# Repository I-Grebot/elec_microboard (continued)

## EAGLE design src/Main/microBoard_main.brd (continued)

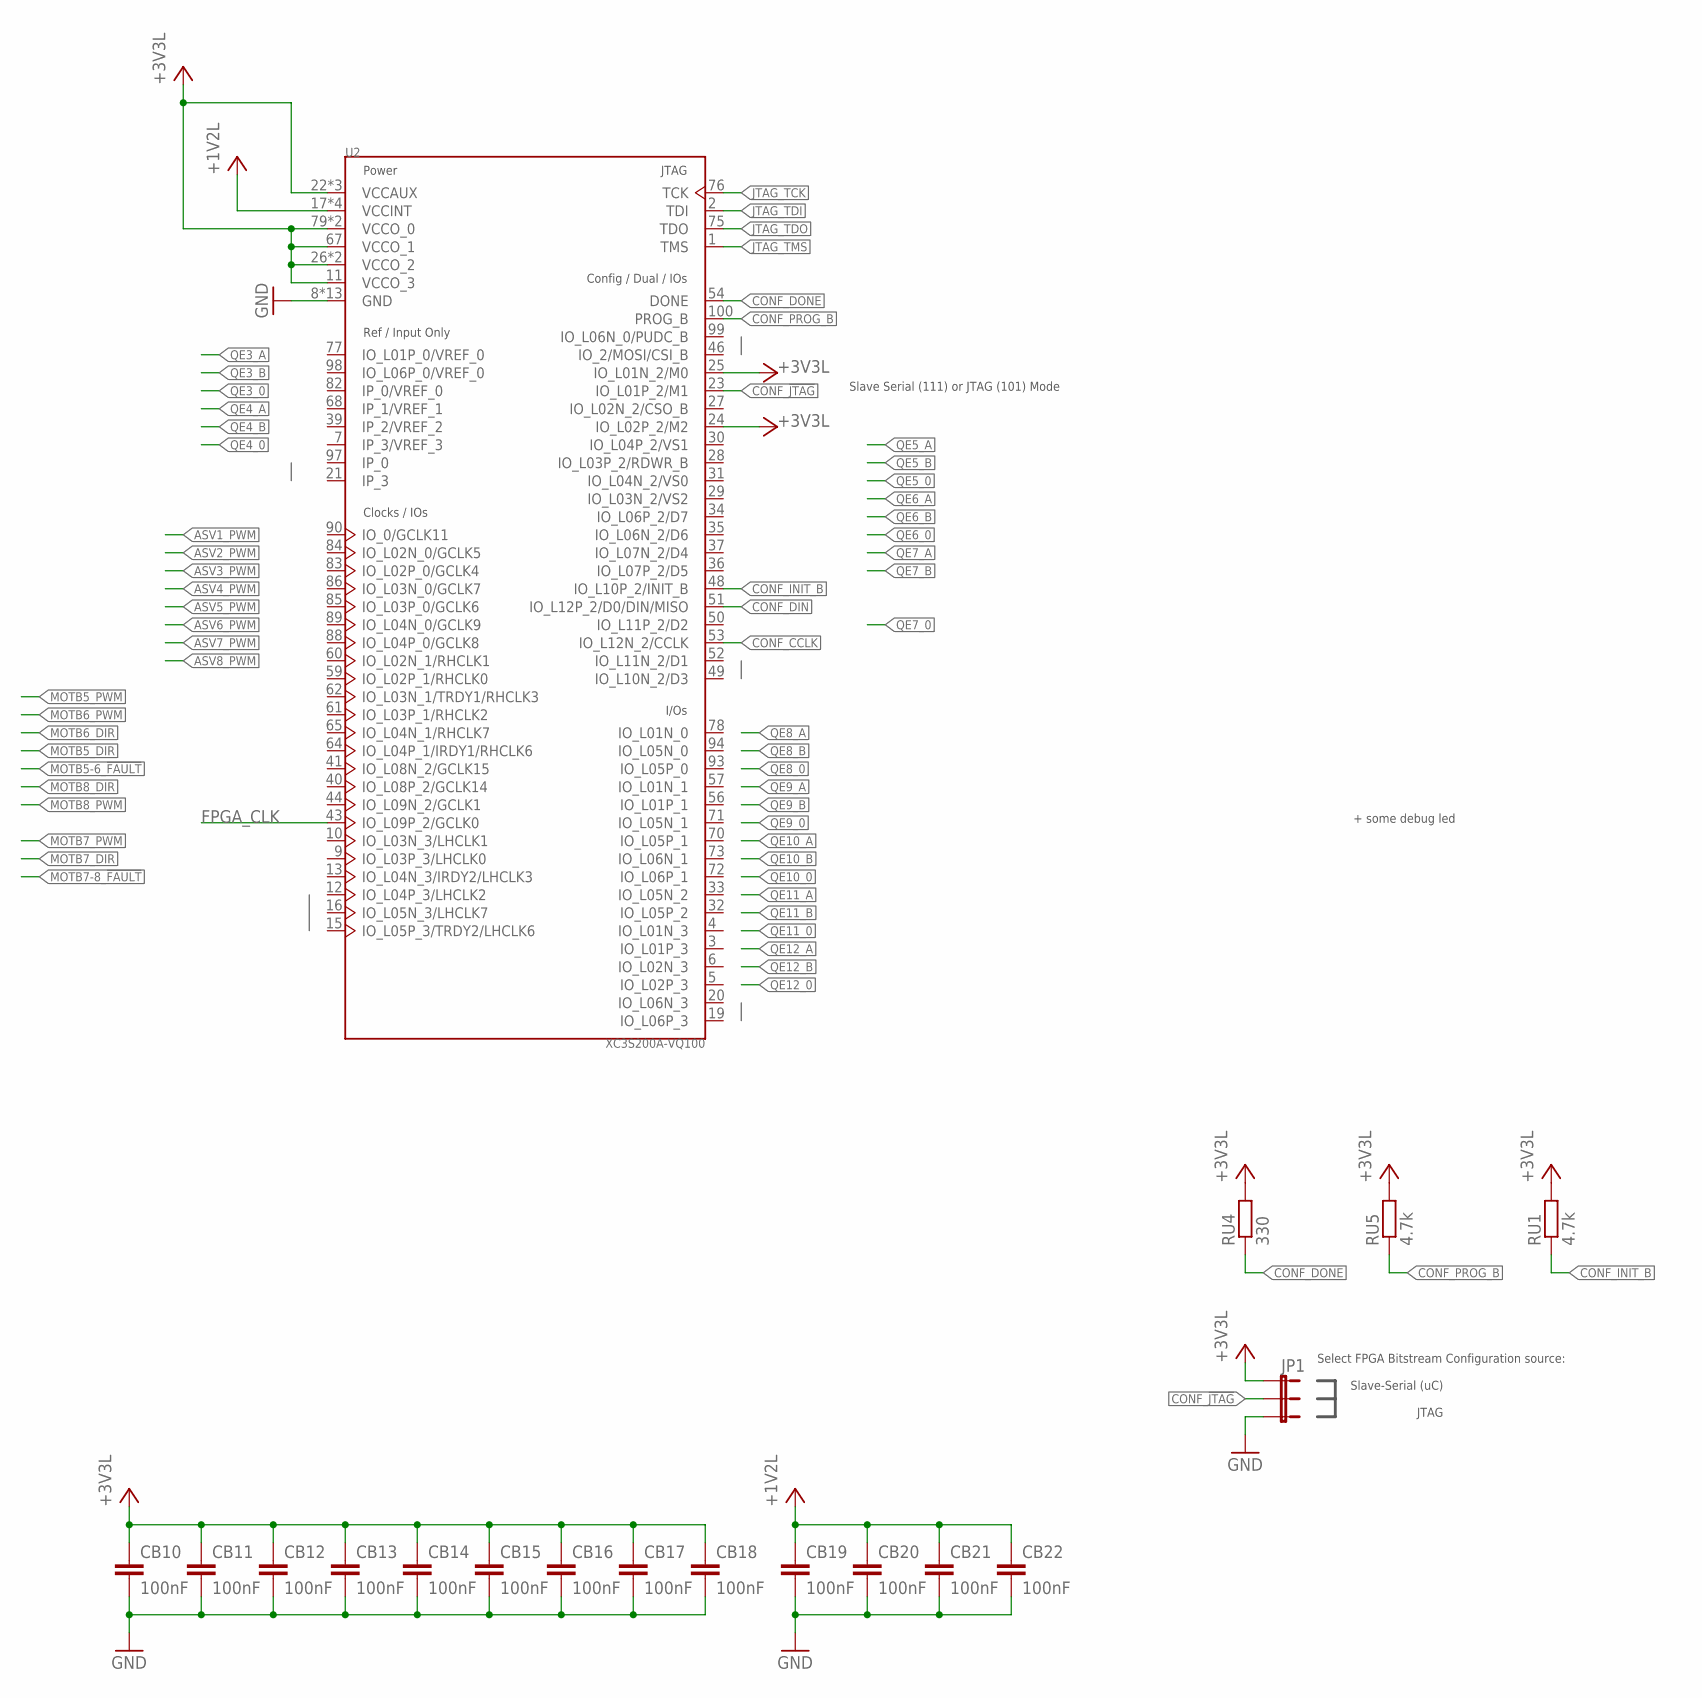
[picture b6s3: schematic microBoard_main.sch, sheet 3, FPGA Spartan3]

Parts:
CB10, CB11, CB12, CB13, CB14, CB15, CB16, CB17, CB18, CB19, CB20, CB21, CB22: 100nF; C0603
JP1: JUMPER-3PTH; 1X03
RU1, RU5: 4.7k; R0603
RU4: 330; R0603
U2: XC3S200A-VQ100; VQFP_100

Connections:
+1V2L: CB19.1, CB20.1, CB21.1, CB22.1, U2.17 (VCCINT), U2.38 (VCCINT), U2.66 (VCCINT), U2.81 (VCCINT); also elsewhere on the board
+3V3L: CB10.1, CB11.1, CB12.1, CB13.1, CB14.1, CB15.1, CB16.1, CB17.1, CB18.1, JP1.1, RU1.2, RU4.2, RU5.2, U2.11 (VCCO_3), U2.22 (VCCAUX), U2.24 (IO_L02P_2/M2), U2.25 (IO_L01N_2/M0), U2.26 (VCCO_2), U2.45 (VCCO_2), U2.55 (VCCAUX), U2.67 (VCCO_1), U2.79 (VCCO_0), U2.92 (VCCAUX), U2.96 (VCCO_0); also elsewhere on the board
CONF_!JTAG!: JP1.2, U2.23 (IO_L01P_2/M1)
CONF_CCLK: U2.53 (IO_L12N_2/CCLK)
CONF_DIN: U2.51 (IO_L12P_2/D0/DIN/MISO)
CONF_DONE: RU4.1, U2.54 (DONE)
CONF_INIT_B: RU1.1, U2.48 (IO_L10P_2/INIT_B)
CONF_PROG_B: RU5.1, U2.100 (PROG_B)
FPGA_CLK: U2.43 (IO_L09P_2/GCLK0)
GND: CB10.2, CB11.2, CB12.2, CB13.2, CB14.2, CB15.2, CB16.2, CB17.2, CB18.2, CB19.2, CB20.2, CB21.2, CB22.2, JP1.3, U2.8 (GND), U2.14 (GND), U2.18 (GND), U2.42 (GND), U2.47 (GND), U2.58 (GND), U2.63 (GND), U2.69 (GND), U2.74 (GND), U2.80 (GND), U2.87 (GND), U2.91 (GND), U2.95 (GND); also elsewhere on the board
JTAG_TCK: U2.76 (TCK); also elsewhere on the board
JTAG_TDI: U2.2 (TDI); also elsewhere on the board
JTAG_TDO: U2.75 (TDO); also elsewhere on the board
JTAG_TMS: U2.1 (TMS); also elsewhere on the board

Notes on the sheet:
Slave Serial (111) or JTAG (101) Mode
Slave-Serial (uC)
JTAG
Select FPGA Bitstream Configuration source:
+ some debug led

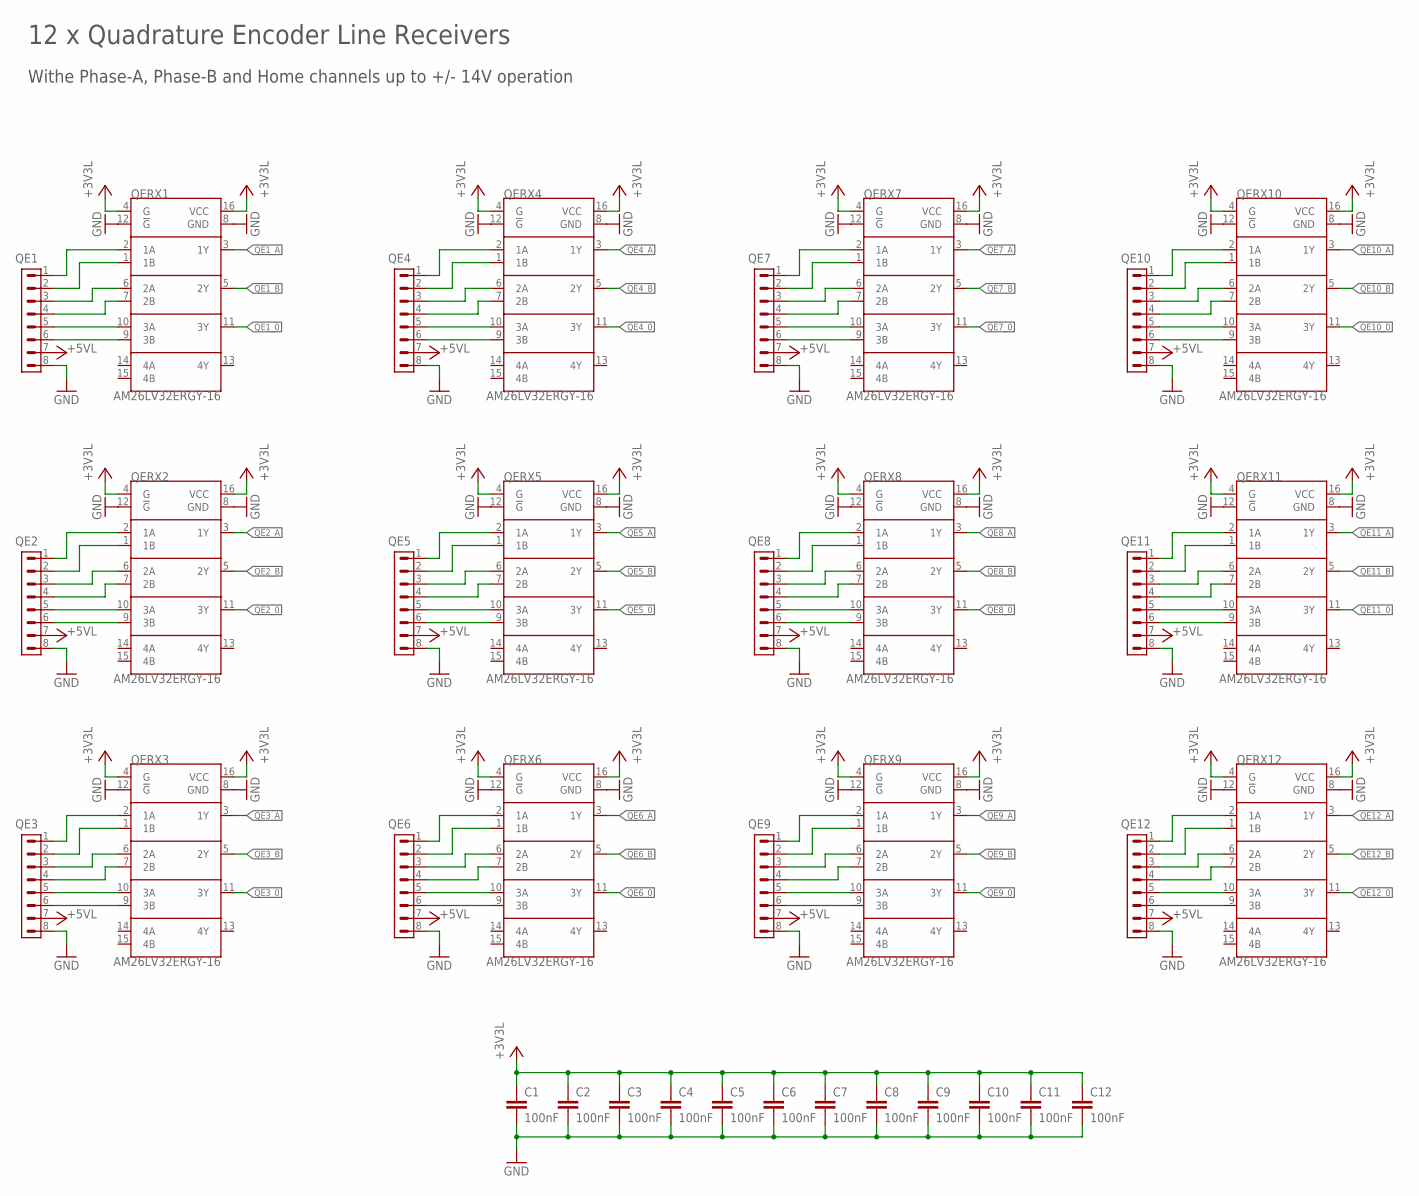
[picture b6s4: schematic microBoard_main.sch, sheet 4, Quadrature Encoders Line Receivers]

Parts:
C1, C2, C3, C4, C5, C6, C7, C8, C9, C10, C11, C12: 100nF; C0603
QE1, QE2, QE3, QE4, QE5, QE6, QE7, QE8, QE9, QE10, QE11, QE12: CON_1.27_8
QERX1, QERX2, QERX3, QERX4, QERX5, QERX6, QERX7, QERX8, QERX9, QERX10, QERX11, QERX12: AM26LV32ERGY-16; RGY_16

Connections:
+3V3L: C1.1, C2.1, C3.1, C4.1, C5.1, C6.1, QERX1.4 (G), QERX1.16 (VCC), QERX2.4 (G), QERX2.16 (VCC), QERX3.4 (G), QERX3.16 (VCC), QERX4.4 (G), QERX4.16 (VCC), QERX5.4 (G), QERX5.16 (VCC), QERX6.4 (G), QERX6.16 (VCC), QERX7.4 (G), QERX7.16 (VCC), QERX8.4 (G), QERX8.16 (VCC), QERX9.4 (G), QERX9.16 (VCC), QERX10.4 (G), QERX10.16 (VCC), QERX11.4 (G), QERX11.16 (VCC), QERX12.4 (G), QERX12.16 (VCC); also elsewhere on the board
+3V3L1: C7.1, C8.1, C9.1, C10.1, C11.1, C12.1
+5VL: QE1.7, QE2.7, QE3.7, QE4.7, QE5.7, QE6.7, QE7.7, QE8.7, QE9.7, QE10.7, QE11.7, QE12.7; also elsewhere on the board
GND: C1.2, C2.2, C3.2, C4.2, C5.2, C6.2, QE1.8, QE2.8, QE3.8, QE4.8, QE5.8, QE6.8, QE7.8, QE8.8, QE9.8, QE10.8, QE11.8, QE12.8, QERX1.8 (GND), QERX1.12 (!G!), QERX2.8 (GND), QERX2.12 (!G!), QERX3.8 (GND), QERX3.12 (!G!), QERX4.8 (GND), QERX4.12 (!G!), QERX5.8 (GND), QERX5.12 (!G!), QERX6.8 (GND), QERX6.12 (!G!), QERX7.8 (GND), QERX7.12 (!G!), QERX8.8 (GND), QERX8.12 (!G!), QERX9.8 (GND), QERX9.12 (!G!), QERX10.8 (GND), QERX10.12 (!G!), QERX11.8 (GND), QERX11.12 (!G!), QERX12.8 (GND), QERX12.12 (!G!); also elsewhere on the board
GND1: C7.2, C8.2, C9.2, C10.2, C11.2, C12.2
unnamed: QE1.4, QERX1.7 (2B)
unnamed: QE1.3, QERX1.6 (2A)
unnamed: QE1.5, QERX1.10 (3A)
unnamed: QE1.6, QERX1.9 (3B)
unnamed: QE1.2, QERX1.1 (1B)
unnamed: QE1.1, QERX1.2 (1A)
unnamed: QE2.5, QERX2.10 (3A)
unnamed: QE2.6, QERX2.9 (3B)
unnamed: QE2.2, QERX2.1 (1B)
unnamed: QE2.1, QERX2.2 (1A)
unnamed: QE2.4, QERX2.7 (2B)
unnamed: QE2.3, QERX2.6 (2A)
unnamed: QE3.5, QERX3.10 (3A)
unnamed: QE3.6, QERX3.9 (3B)
unnamed: QE3.2, QERX3.1 (1B)
unnamed: QE3.1, QERX3.2 (1A)
unnamed: QE3.4, QERX3.7 (2B)
unnamed: QE3.3, QERX3.6 (2A)
unnamed: QE4.5, QERX4.10 (3A)
unnamed: QE4.6, QERX4.9 (3B)
unnamed: QE4.2, QERX4.1 (1B)
unnamed: QE4.1, QERX4.2 (1A)
unnamed: QE4.4, QERX4.7 (2B)
unnamed: QE4.3, QERX4.6 (2A)
unnamed: QE5.5, QERX5.10 (3A)
unnamed: QE5.6, QERX5.9 (3B)
unnamed: QE5.2, QERX5.1 (1B)
unnamed: QE5.1, QERX5.2 (1A)
unnamed: QE5.4, QERX5.7 (2B)
unnamed: QE5.3, QERX5.6 (2A)
unnamed: QE6.5, QERX6.10 (3A)
unnamed: QE6.6, QERX6.9 (3B)
unnamed: QE6.2, QERX6.1 (1B)
unnamed: QE6.1, QERX6.2 (1A)
unnamed: QE6.4, QERX6.7 (2B)
unnamed: QE6.3, QERX6.6 (2A)
unnamed: QE7.5, QERX7.10 (3A)
unnamed: QE7.6, QERX7.9 (3B)
unnamed: QE7.2, QERX7.1 (1B)
unnamed: QE7.1, QERX7.2 (1A)
unnamed: QE7.4, QERX7.7 (2B)
unnamed: QE7.3, QERX7.6 (2A)
unnamed: QE8.5, QERX8.10 (3A)
unnamed: QE8.6, QERX8.9 (3B)
unnamed: QE8.2, QERX8.1 (1B)
unnamed: QE8.1, QERX8.2 (1A)
unnamed: QE8.4, QERX8.7 (2B)
unnamed: QE8.3, QERX8.6 (2A)
unnamed: QE9.5, QERX9.10 (3A)
unnamed: QE9.6, QERX9.9 (3B)
unnamed: QE9.2, QERX9.1 (1B)
unnamed: QE9.1, QERX9.2 (1A)
unnamed: QE9.4, QERX9.7 (2B)
unnamed: QE9.3, QERX9.6 (2A)
unnamed: QE10.5, QERX10.10 (3A)
unnamed: QE10.6, QERX10.9 (3B)
unnamed: QE10.2, QERX10.1 (1B)
unnamed: QE10.1, QERX10.2 (1A)
unnamed: QE10.4, QERX10.7 (2B)
unnamed: QE10.3, QERX10.6 (2A)
unnamed: QE11.5, QERX11.10 (3A)
unnamed: QE11.6, QERX11.9 (3B)
unnamed: QE11.2, QERX11.1 (1B)
unnamed: QE11.1, QERX11.2 (1A)
unnamed: QE11.4, QERX11.7 (2B)
unnamed: QE11.3, QERX11.6 (2A)
unnamed: QE12.5, QERX12.10 (3A)
unnamed: QE12.6, QERX12.9 (3B)
unnamed: QE12.2, QERX12.1 (1B)
unnamed: QE12.1, QERX12.2 (1A)
unnamed: QE12.4, QERX12.7 (2B)
unnamed: QE12.3, QERX12.6 (2A)
QE1_0: QERX1.11 (3Y)
QE1_A: QERX1.3 (1Y)
QE1_B: QERX1.5 (2Y)
QE2_0: QERX2.11 (3Y)
QE2_A: QERX2.3 (1Y)
QE2_B: QERX2.5 (2Y)
QE3_0: QERX3.11 (3Y)
QE3_A: QERX3.3 (1Y)
QE3_B: QERX3.5 (2Y)
QE4_0: QERX4.11 (3Y)
QE4_A: QERX4.3 (1Y)
QE4_B: QERX4.5 (2Y)
QE5_0: QERX5.11 (3Y)
QE5_A: QERX5.3 (1Y)
QE5_B: QERX5.5 (2Y)
QE6_0: QERX6.11 (3Y)
QE6_A: QERX6.3 (1Y)
QE6_B: QERX6.5 (2Y)
QE7_0: QERX7.11 (3Y)
QE7_A: QERX7.3 (1Y)
QE7_B: QERX7.5 (2Y)
QE8_0: QERX8.11 (3Y)
QE8_A: QERX8.3 (1Y)
QE8_B: QERX8.5 (2Y)
QE9_0: QERX9.11 (3Y)
QE9_A: QERX9.3 (1Y)
QE9_B: QERX9.5 (2Y)
QE10_0: QERX10.11 (3Y)
QE10_A: QERX10.3 (1Y)
QE10_B: QERX10.5 (2Y)
QE11_0: QERX11.11 (3Y)
QE11_A: QERX11.3 (1Y)
QE11_B: QERX11.5 (2Y)
QE12_0: QERX12.11 (3Y)
QE12_A: QERX12.3 (1Y)
QE12_B: QERX12.5 (2Y)

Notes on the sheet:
12 x Quadrature Encoder Line Receivers
Withe Phase-A, Phase-B and Home channels up to +/- 14V operation

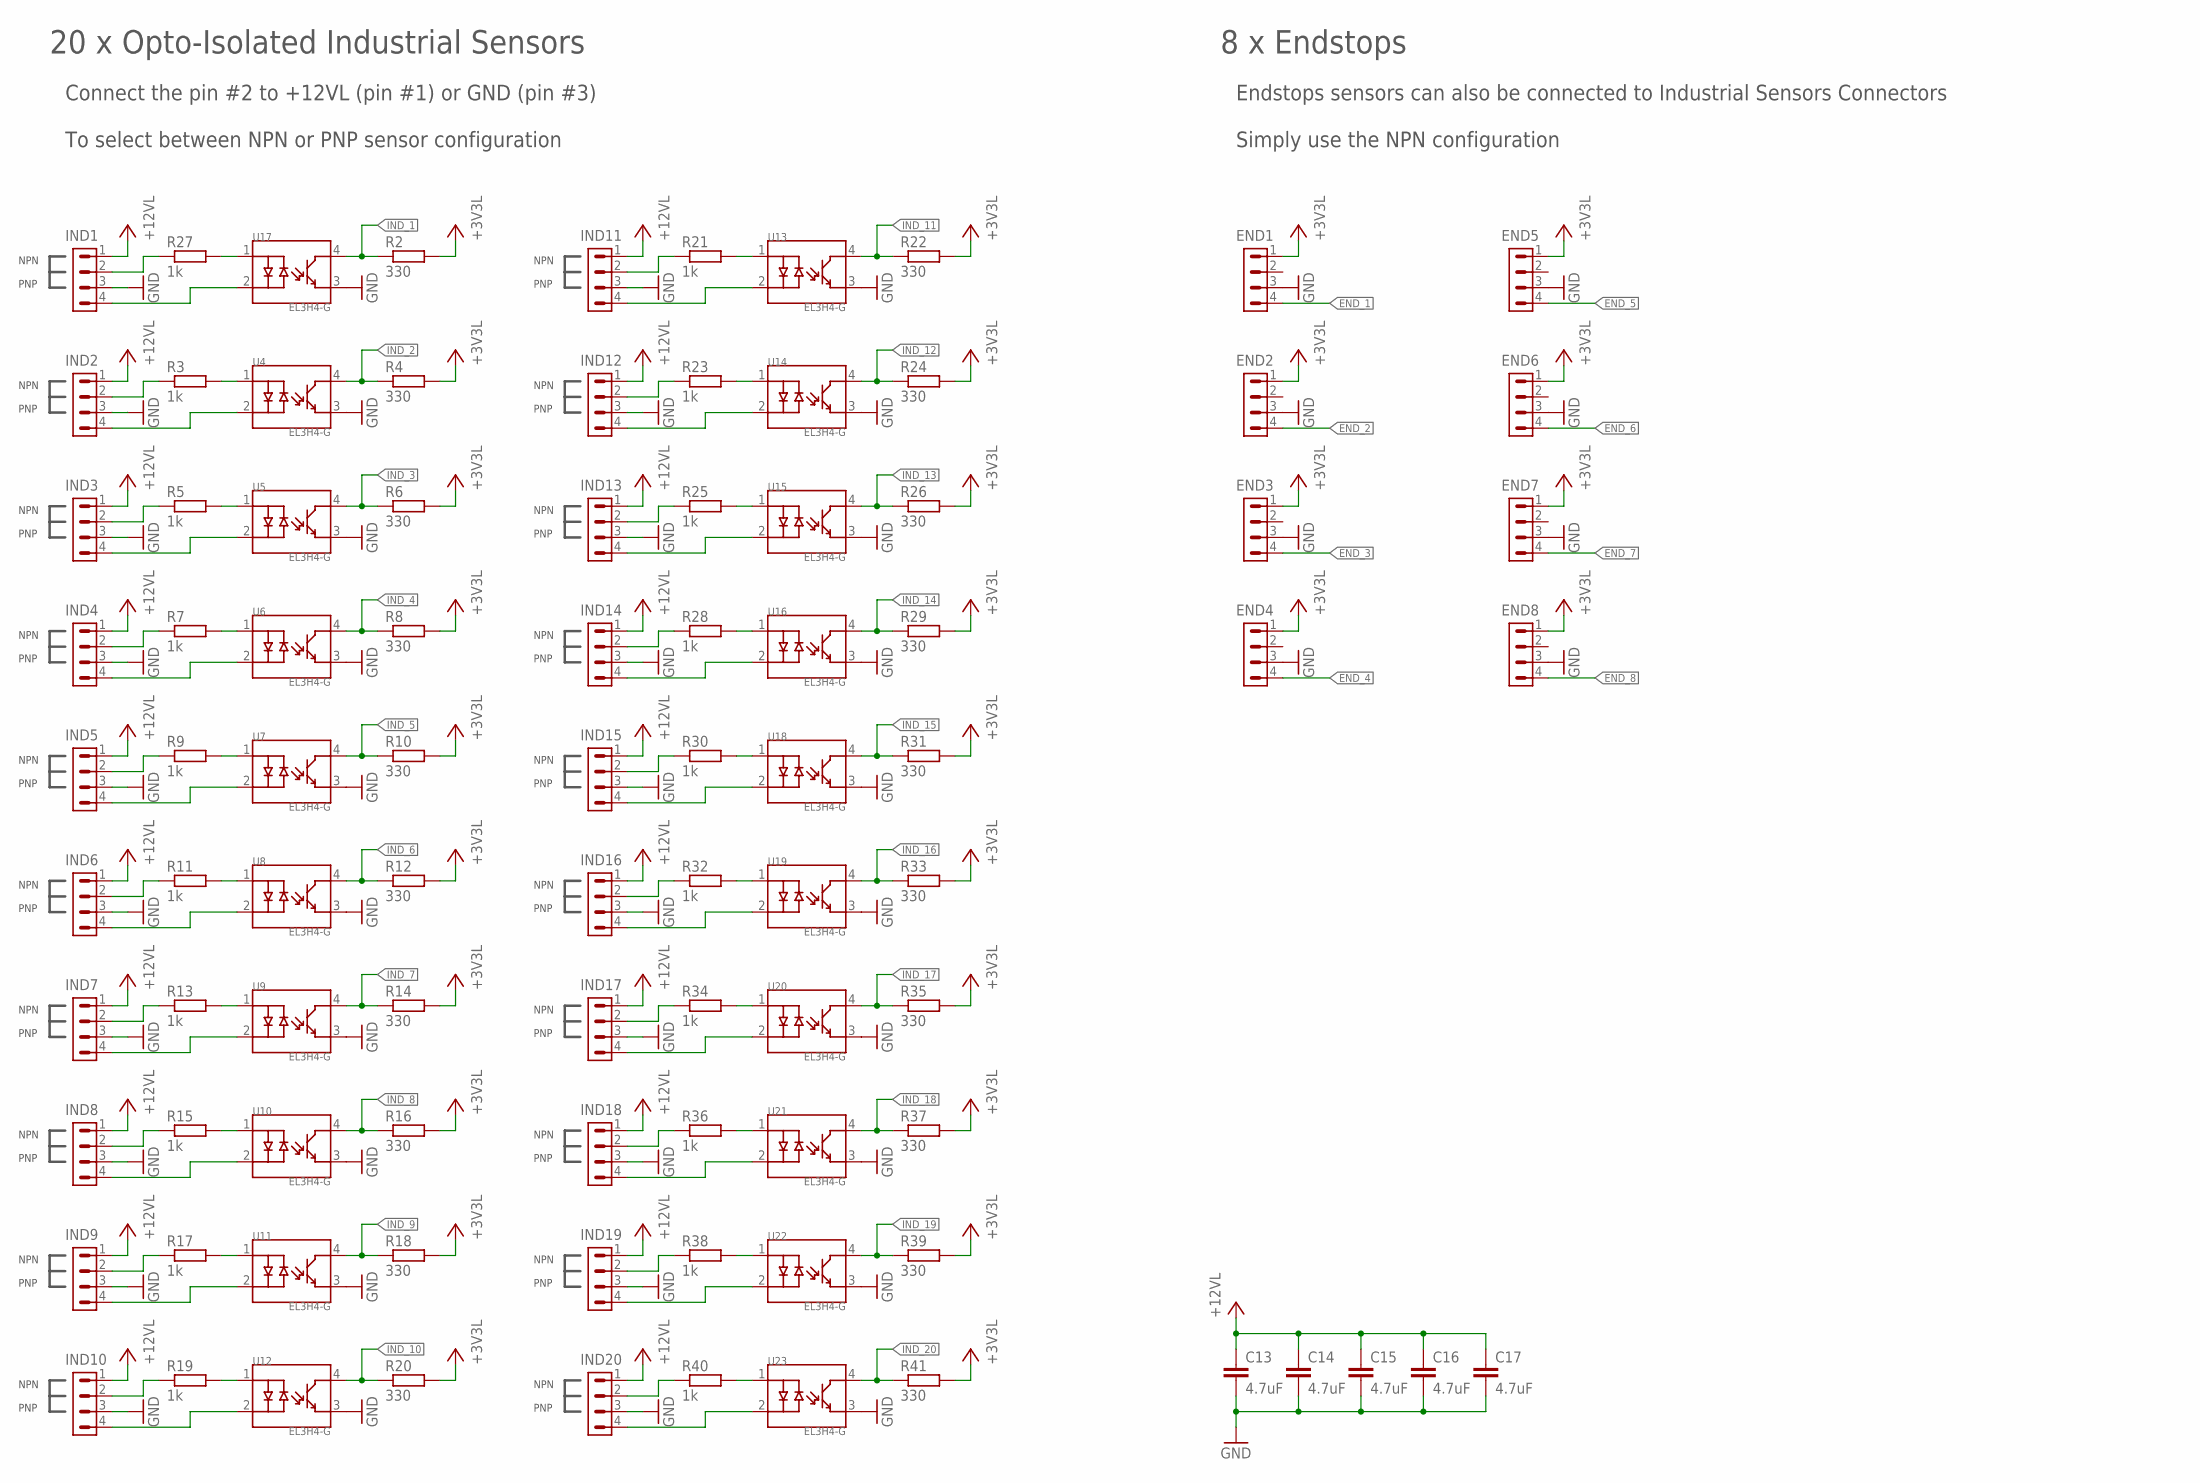
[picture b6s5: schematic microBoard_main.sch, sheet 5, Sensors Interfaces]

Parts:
C13, C14, C15, C16, C17: 4.7uF; C1206
END1, END2, END3, END4, END5, END6, END7, END8: CON_1.27_4
IND1, IND2, IND3, IND4, IND5, IND6, IND7, IND8, IND9, IND10, IND11, IND12, IND13, IND14, IND15, IND16, IND17, IND18, IND19, IND20: CON_1.27_4
R2, R4, R6, R8, R10, R12, R14, R16, R18, R20, R22, R24, R26, R29, R31, R33, R35, R37, R39, R41: 330; R0603
R3, R5, R7, R9, R11, R13, R15, R17, R19, R21, R23, R25, R27, R28, R30, R32, R34, R36, R38, R40: 1k; R0603
U4, U5, U6, U7, U8, U9, U10, U11, U12, U13, U14, U15, U16, U17, U18, U19, U20, U21, U22, U23: EL3H4-G; SSOP_4

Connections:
+3V3L: END1.1, END2.1, END3.1, END4.1, END5.1, END6.1, END7.1, END8.1, R2.2, R4.2, R6.2, R8.2, R10.2, R12.2, R14.2, R16.2, R18.2, R20.2, R22.2, R24.2, R26.2, R29.2, R31.2, R33.2, R35.2, R37.2, R39.2, R41.2; also elsewhere on the board
+12VL: C13.1, C14.1, C15.1, C16.1, C17.1, IND1.1, IND2.1, IND3.1, IND4.1, IND5.1, IND6.1, IND7.1, IND8.1, IND9.1, IND10.1, IND11.1, IND12.1, IND13.1, IND14.1, IND15.1, IND16.1, IND17.1, IND18.1, IND19.1, IND20.1; also elsewhere on the board
END_1: END1.4
END_2: END2.4
END_3: END3.4
END_4: END4.4
END_5: END5.4
END_6: END6.4
END_7: END7.4
END_8: END8.4
GND: C13.2, C14.2, C15.2, C16.2, C17.2, END1.3, END2.3, END3.3, END4.3, END5.3, END6.3, END7.3, END8.3, IND1.3, IND2.3, IND3.3, IND4.3, IND5.3, IND6.3, IND7.3, IND8.3, IND9.3, IND10.3, IND11.3, IND12.3, IND13.3, IND14.3, IND15.3, IND16.3, IND17.3, IND18.3, IND19.3, IND20.3, U4.3, U5.3, U6.3, U7.3, U8.3, U9.3, U10.3, U11.3, U12.3, U13.3, U14.3, U15.3, U16.3, U17.3, U18.3, U19.3, U20.3, U21.3, U22.3, U23.3; also elsewhere on the board
IND_1: R2.1, U17.4
IND_2: R4.1, U4.4
IND_3: R6.1, U5.4
IND_4: R8.1, U6.4
IND_5: R10.1, U7.4
IND_6: R12.1, U8.4
IND_7: R14.1, U9.4
IND_8: R16.1, U10.4
IND_9: R18.1, U11.4
IND_10: R20.1, U12.4
IND_11: R22.1, U13.4
IND_12: R24.1, U14.4
IND_13: R26.1, U15.4
IND_14: R29.1, U16.4
IND_15: R31.1, U18.4
IND_16: R33.1, U19.4
IND_17: R35.1, U20.4
IND_18: R37.1, U21.4
IND_19: R39.1, U22.4
IND_20: R41.1, U23.4
unnamed: IND1.4, U17.2
unnamed: IND1.2, R27.1
unnamed: R27.2, U17.1
unnamed: IND2.2, R3.1
unnamed: R3.2, U4.1
unnamed: IND2.4, U4.2
unnamed: IND3.2, R5.1
unnamed: R5.2, U5.1
unnamed: IND3.4, U5.2
unnamed: IND4.2, R7.1
unnamed: R7.2, U6.1
unnamed: IND4.4, U6.2
unnamed: IND5.2, R9.1
unnamed: R9.2, U7.1
unnamed: IND5.4, U7.2
unnamed: IND6.2, R11.1
unnamed: R11.2, U8.1
unnamed: IND6.4, U8.2
unnamed: IND7.2, R13.1
unnamed: R13.2, U9.1
unnamed: IND7.4, U9.2
unnamed: IND8.2, R15.1
unnamed: R15.2, U10.1
unnamed: IND8.4, U10.2
unnamed: IND9.2, R17.1
unnamed: R17.2, U11.1
unnamed: IND9.4, U11.2
unnamed: IND10.2, R19.1
unnamed: R19.2, U12.1
unnamed: IND10.4, U12.2
unnamed: IND11.2, R21.1
unnamed: R21.2, U13.1
unnamed: IND11.4, U13.2
unnamed: IND12.2, R23.1
unnamed: R23.2, U14.1
unnamed: IND12.4, U14.2
unnamed: IND13.2, R25.1
unnamed: R25.2, U15.1
unnamed: IND13.4, U15.2
unnamed: IND14.2, R28.1
unnamed: R28.2, U16.1
unnamed: IND14.4, U16.2
unnamed: IND15.2, R30.1
unnamed: R30.2, U18.1
unnamed: IND15.4, U18.2
unnamed: IND16.2, R32.1
unnamed: R32.2, U19.1
unnamed: IND16.4, U19.2
unnamed: IND17.2, R34.1
unnamed: R34.2, U20.1
unnamed: IND17.4, U20.2
unnamed: IND18.2, R36.1
unnamed: R36.2, U21.1
unnamed: IND18.4, U21.2
unnamed: IND19.2, R38.1
unnamed: R38.2, U22.1
unnamed: IND19.4, U22.2
unnamed: IND20.2, R40.1
unnamed: R40.2, U23.1
unnamed: IND20.4, U23.2

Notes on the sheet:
20 x Opto-Isolated Industrial Sensors
8 x Endstops
NPN
PNP
Connect the pin #2 to +12VL (pin #1) or GND (pin #3)
To select between NPN or PNP sensor configuration
Endstops sensors can also be connected to Industrial Sensors Connectors
Simply use the NPN configuration

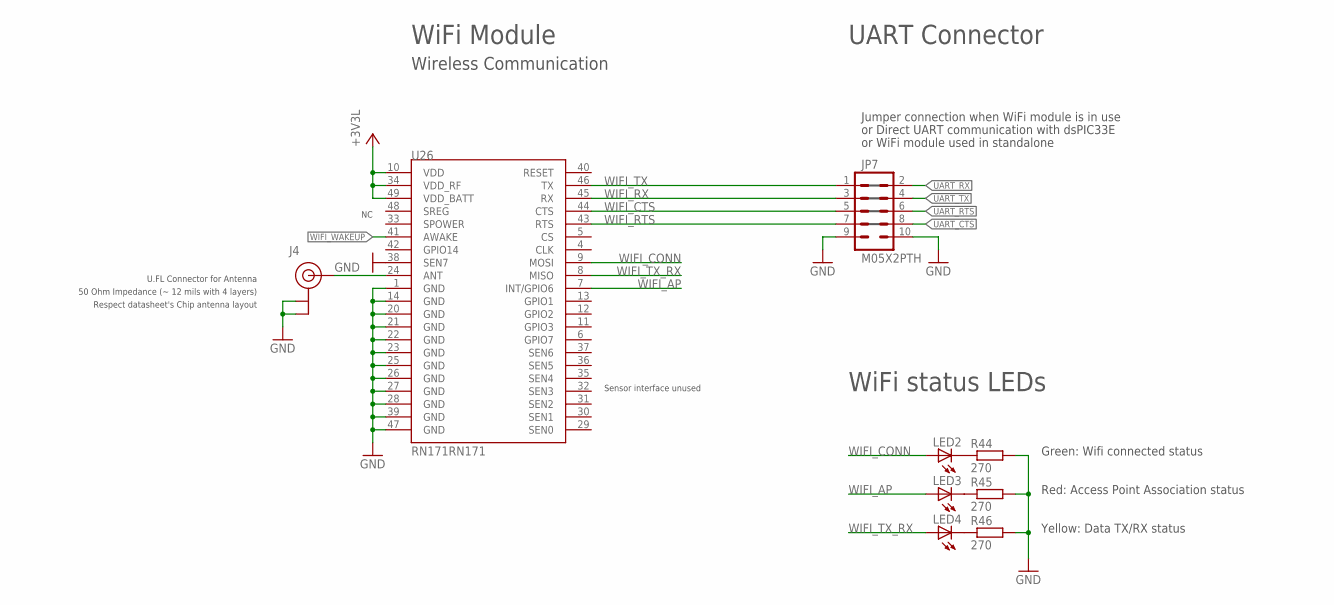
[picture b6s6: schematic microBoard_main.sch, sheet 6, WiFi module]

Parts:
J4: U.FL
JP7: M05X2PTH; AVR_ICSP
LED2, LED3, LED4: LEDCHIP-LED0805; CHIP-LED0805
R44, R45, R46: 270; R0603
U26: RN171RN171; RN171

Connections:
+3V3L: U26.10 (VDD), U26.34 (VDD_RF), U26.49 (VDD_BATT); also elsewhere on the board
GND: J4.P$1 (GND), J4.P$2 (GND), JP7.9, JP7.10, R44.2, R45.2, R46.2, U26.1 (GND), U26.14 (GND), U26.20 (GND), U26.21 (GND), U26.22 (GND), U26.23 (GND), U26.25 (GND), U26.26 (GND), U26.27 (GND), U26.28 (GND), U26.38 (SEN7), U26.39 (GND), U26.47 (GND); also elsewhere on the board
unnamed: LED2.C, R44.1
unnamed: LED3.C, R45.1
unnamed: LED4.C, R46.1
unnamed: J4.P$3 (SIGNAL), U26.24 (ANT)
UART_CTS: JP7.8
UART_RTS: JP7.6
UART_RX: JP7.2
UART_TX: JP7.4
WIFI_AP: LED3.A, U26.7 (INT/GPIO6)
WIFI_CONN: LED2.A, U26.9 (MOSI)
WIFI_CTS: JP7.5, U26.44 (CTS)
WIFI_RTS: JP7.7, U26.43 (RTS)
WIFI_RX: JP7.3, U26.45 (RX)
WIFI_TX: JP7.1, U26.46 (TX)
WIFI_TX_RX: LED4.A, U26.8 (MISO)
WIFI_WAKEUP: U26.41 (AWAKE)

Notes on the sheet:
Wireless Communication
WiFi Module
UART Connector
Sensor interface unused
50 Ohm Impedance (~ 12 mils with 4 layers)
Green: Wifi connected status
Yellow: Data TX/RX status
Red: Access Point Association status
Respect datasheet's Chip antenna layout
U.FL Connector for Antenna
Jumper connection when WiFi module is in use
or Direct UART communication with dsPIC33E
or WiFi module used in standalone
WiFi status LEDs

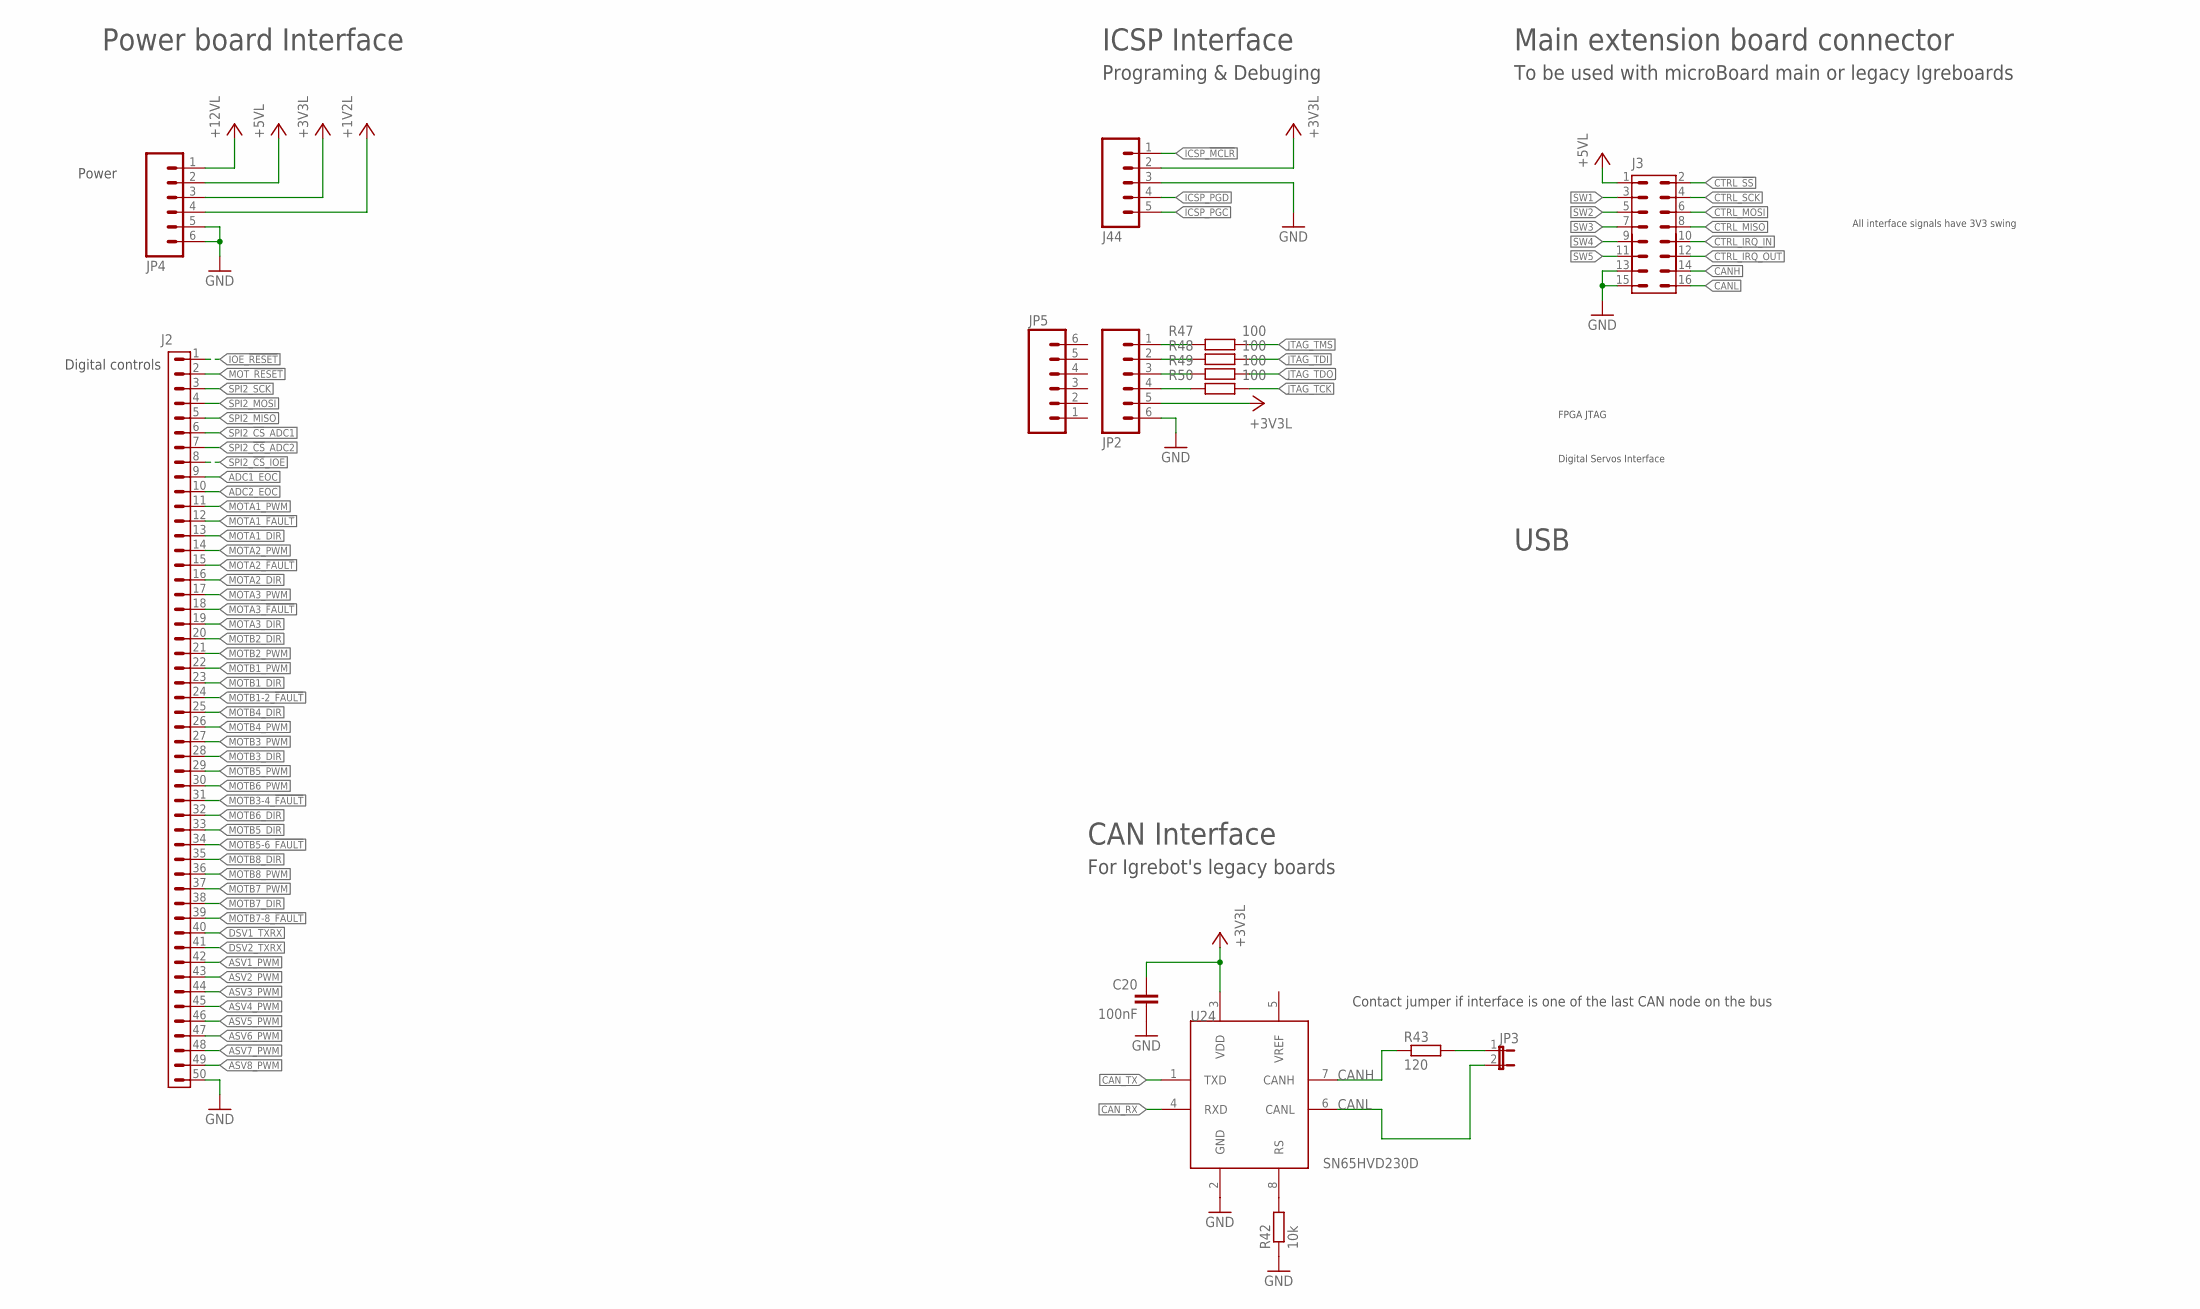
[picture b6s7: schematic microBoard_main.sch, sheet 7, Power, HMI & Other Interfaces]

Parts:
C20: 100nF; C0603
J2: FFC-0.5_50; FFC-SMD-0.5_50
J3: HE10_H_16; CON_2X_2.54_H_16
J44: M05LOCK; 1X05_LOCK
JP2, JP4: M06LOCK; 1X06_LOCK
JP3: JUMPER-2PTH_LOCK; 1X02_LOCK
JP5: M06SMD-1MM; 1X06-1MM
R42: 10k; R0603
R43: 120; R0603
R47, R48, R49, R50: 100; R0603
U24: SN65HVD230D; SO-08

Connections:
+1V2L: JP4.4; also elsewhere on the board
+3V3L: C20.1, J44.2, JP2.5, JP4.3, U24.3 (VDD); also elsewhere on the board
+5VL: J3.1, JP4.2; also elsewhere on the board
+12VL: JP4.1; also elsewhere on the board
ADC1_EOC: J2.9
ADC2_EOC: J2.10
ASV1_PWM: J2.42
ASV2_PWM: J2.43
ASV3_PWM: J2.44
ASV4_PWM: J2.45
ASV5_PWM: J2.46
ASV6_PWM: J2.47
ASV7_PWM: J2.48
ASV8_PWM: J2.49
CANH: J3.14, R43.1, U24.7 (CANH)
CANL: J3.16, JP3.2, U24.6 (CANL)
CAN_RX: U24.4 (RXD)
CAN_TX: U24.1 (TXD)
CTRL_!SS!: J3.2
CTRL_IRQ_IN: J3.10
CTRL_IRQ_OUT: J3.12
CTRL_MISO: J3.8
CTRL_MOSI: J3.6
CTRL_SCK: J3.4
DSV1_TXRX: J2.40
DSV2_TXRX: J2.41
GND: C20.2, J2.50, J3.13, J3.15, J44.3, JP2.6, JP4.5, JP4.6, R42.1, U24.2 (GND); also elsewhere on the board
ICSP_!MCLR!: J44.1; also elsewhere on the board
ICSP_PGC: J44.5; also elsewhere on the board
ICSP_PGD: J44.4; also elsewhere on the board
IOE_!RESET!: J2.1
JTAG_TCK: R50.2; also elsewhere on the board
JTAG_TDI: R48.2; also elsewhere on the board
JTAG_TDO: R49.2; also elsewhere on the board
JTAG_TMS: R47.2; also elsewhere on the board
MOTA1_!FAULT!: J2.12
MOTA1_DIR: J2.13
MOTA1_PWM: J2.11
MOTA2_!FAULT!: J2.15
MOTA2_DIR: J2.16
MOTA2_PWM: J2.14
MOTA3_!FAULT!: J2.18
MOTA3_DIR: J2.19
MOTA3_PWM: J2.17
MOTB1-2_!FAULT!: J2.24
MOTB1_DIR: J2.23
MOTB1_PWM: J2.22
MOTB2_DIR: J2.20
MOTB2_PWM: J2.21
MOTB3-4_!FAULT!: J2.31
MOTB3_DIR: J2.28
MOTB3_PWM: J2.27
MOTB4_DIR: J2.25
MOTB4_PWM: J2.26
MOTB5-6_!FAULT!: J2.34
MOTB5_DIR: J2.33
MOTB5_PWM: J2.29
MOTB6_DIR: J2.32
MOTB6_PWM: J2.30
MOTB7-8_!FAULT!: J2.39
MOTB7_DIR: J2.38
MOTB7_PWM: J2.37
MOTB8_DIR: J2.35
MOTB8_PWM: J2.36
MOT_!RESET!: J2.2
unnamed: R42.2, U24.8 (RS)
unnamed: JP3.1, R43.2
unnamed: JP2.2, R48.1
unnamed: JP2.1, R47.1
unnamed: JP2.3, R49.1
unnamed: JP2.4, R50.1
SPI2_!CS!_ADC1: J2.6
SPI2_!CS!_ADC2: J2.7
SPI2_!CS!_IOE: J2.8
SPI2_MISO: J2.5
SPI2_MOSI: J2.4
SPI2_SCK: J2.3
SW1: J3.3
SW2: J3.5
SW3: J3.7
SW4: J3.9
SW5: J3.11

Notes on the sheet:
Power
Digital controls
FPGA JTAG
Digital Servos Interface
To be used with microBoard main or legacy Igreboards
Main extension board connector
All interface signals have 3V3 swing
Programing & Debuging
ICSP Interface
For Igrebot's legacy boards
CAN Interface
Contact jumper if interface is one of the last CAN node on the bus
Power board Interface
USB

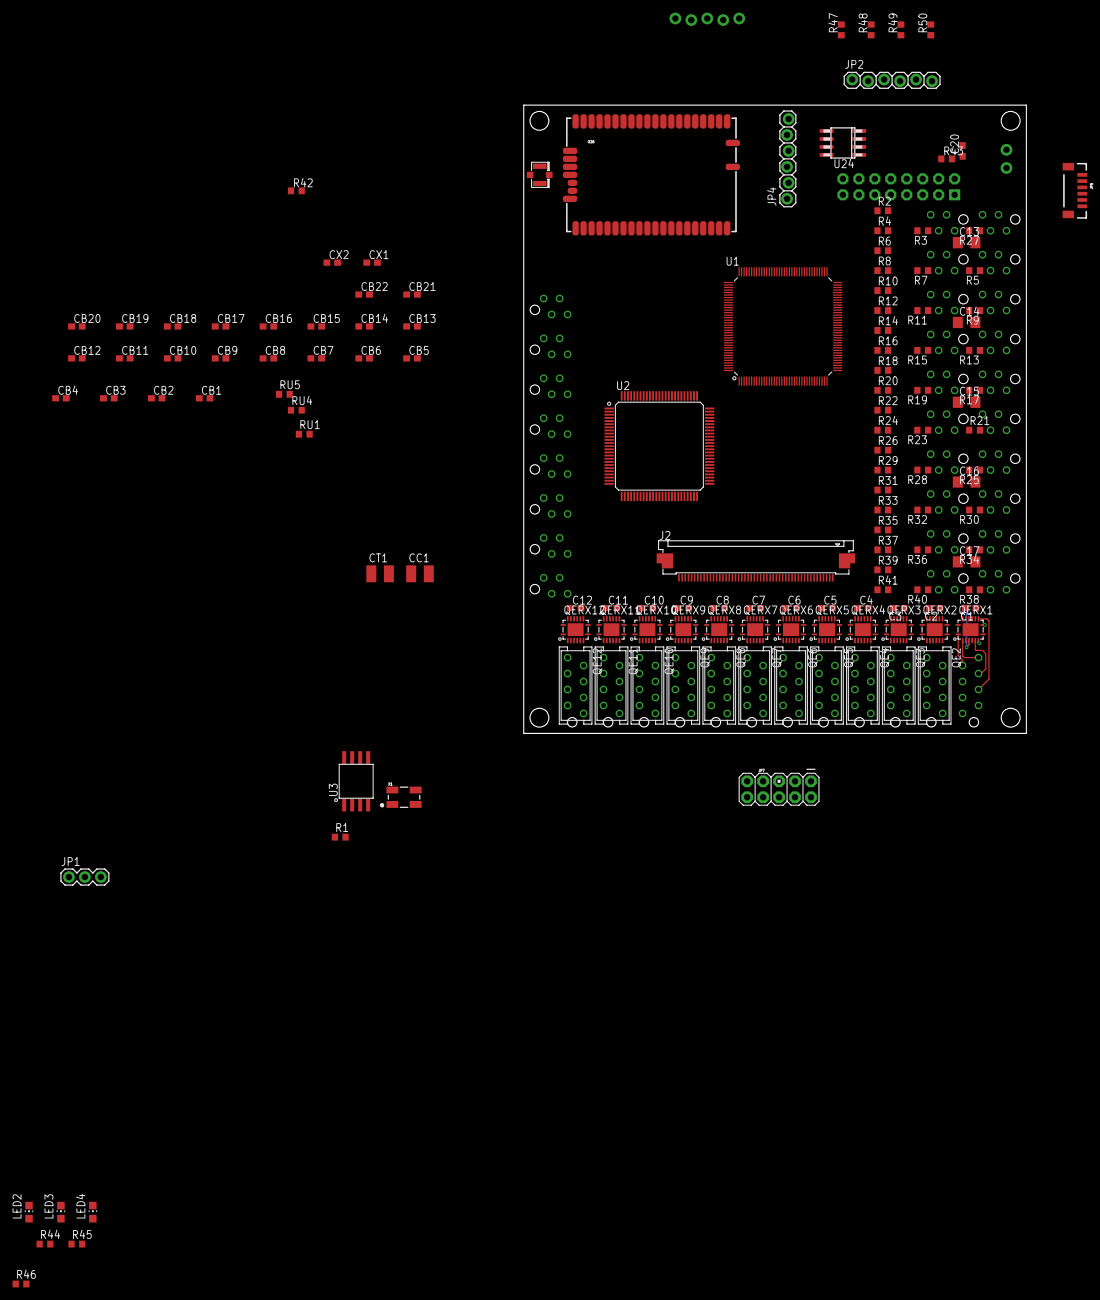
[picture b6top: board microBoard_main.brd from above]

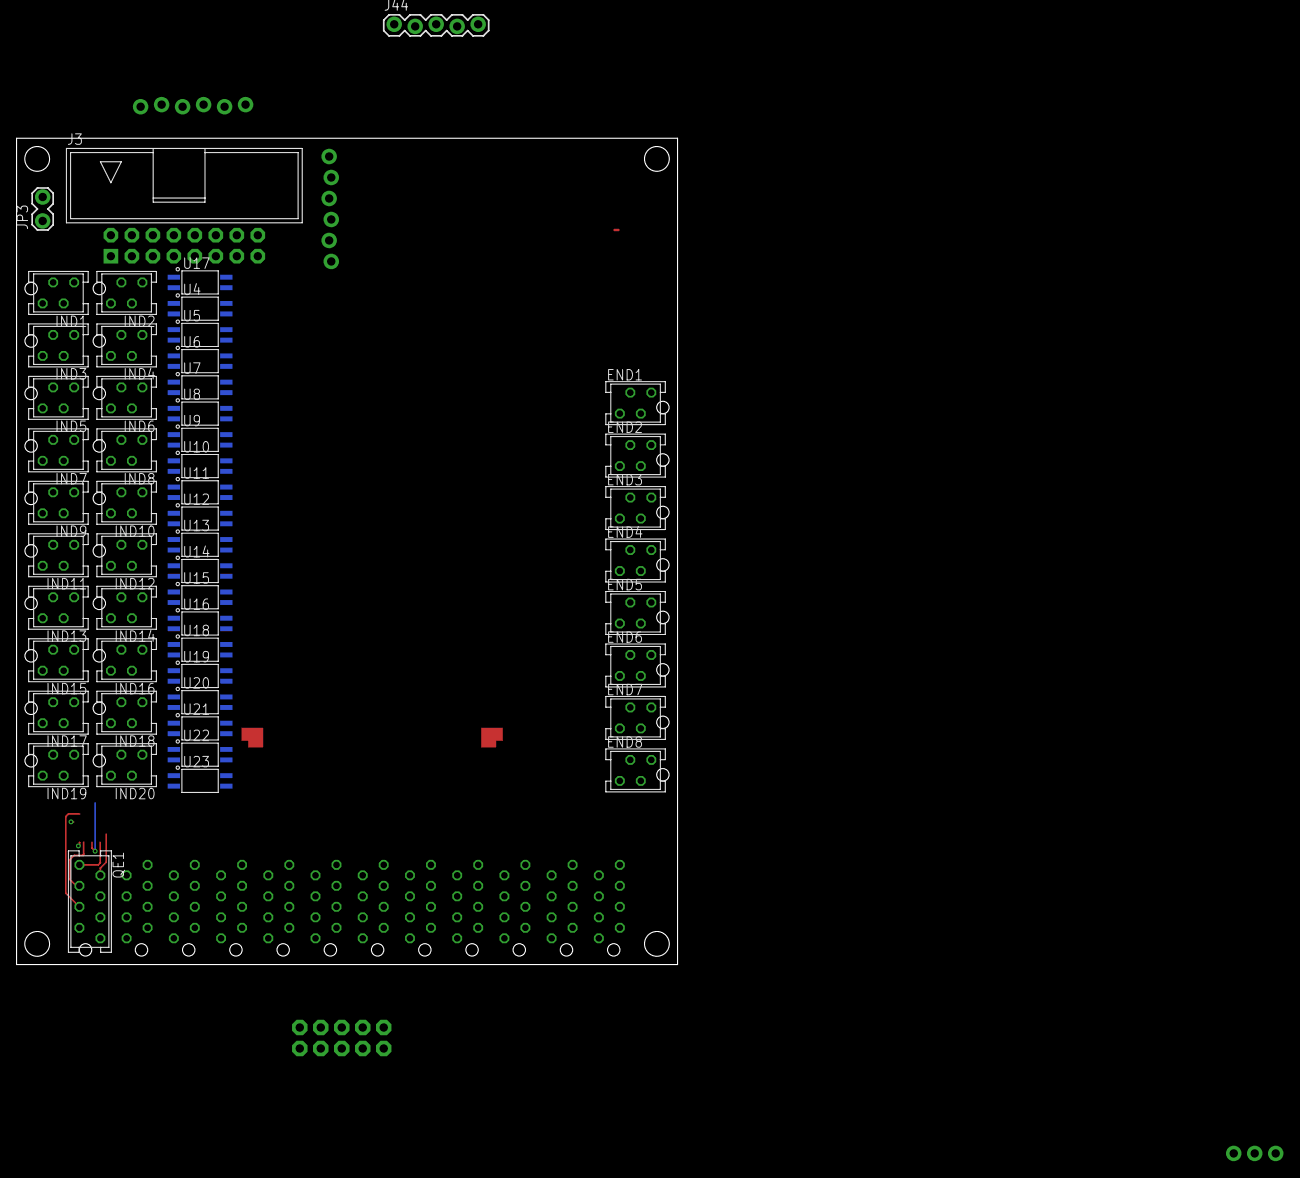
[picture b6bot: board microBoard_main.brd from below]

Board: 4 copper layers, 80.0 x 100.0 mm, 188 parts (52 on the bottom side), 194 nets.

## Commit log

2016-11-11 Import from SVN
